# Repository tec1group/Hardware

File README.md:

This Repository is for all files that relate to the hardware of the TEC-1:
- Any expansion boards suitable for the TEC-1
- Any alternative/derivative motherboards to the TEC-1.
- and possibly any other Z80-based motherboards (eg. SC-1) and their expansions, although they should all be grouped in one folder.

<h1>How to Use this Repo</h1>
1. Make a FORK of this Repo to your own account. (You know you want to.)

That's right, make a Fork of this entire Repo back to your account.

Please keep the existing folder structure intact. If it isn't your folder, don't rename it or move it. Leave it be. Or if you don't want it, feel free to delete it from *your* Repo, but then your Pull Request (see below) may be difficult to follow/allow, if they try to remove files from the Master.

<h2>KEEPING UP TO DATE</h2>
When others add to the Repo, you'll probably want an up to date copy. (You don't have to, though.)

1. At the top right of the Repo, you will see a button called "Fetch upstream". Go on, click it...

2. You will be presented with two options, one is to "Compare" and the other is "Fetch and Merge"

3. Click on "Fetch and Merge". (If there are folders you don't care to have, you can dleete them from your own copy of the repo.)

<h2>ADDING TO THE REPO</h2>
When you want to Add or make Changes to the Repo.

1. Create a Folder in *your copy* of the Repo for each board or if it makes sense, group of boards connected to a single project.

2. Do your thing and create the hardware files in that folder; Schematics, Gerbers, documentation, PCB Layouts... Whatever it is you want to share and include into the TEC1group Hardware repository.

3. Once you are done with all your changes and ready to share it with the Group, click on the "Contribute" button and then "Open pull request".

4. A page called "Comparing changes" appears, highlighting the new files you want to add. Again, click on "Create pull request".

5. And yet another page, this time giving you the option to edit the "commit comments" that the Admins of the TEC1group will read before approval of the merge. Last time, click on "Create pull request".

6. You will be taken to the list of Pull Requests for the Repo and see how many are outstanding etc.

7. The admins of the TEC1group will review your changes and as long as you keep the changes to a folder *you* created and maintain, then there is very little reason for them to not accept the changes and pull your work back to the master Repo for all and sundry to share. THANK YOU!

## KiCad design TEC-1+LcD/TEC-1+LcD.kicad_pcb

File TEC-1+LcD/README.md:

<h1>TEC-1+LcD</h1>

This schematic and assocated files, suitable for use with KiCAD, is based on a TEC-1D with the addon of the LCD section of the DAT board.

It also has in input switch bank that can be used for user input during a program, but the main thought behind it is for setting options that would be read at startup, like what Keyboard layout to use, or what ROM to copy in.

Lastly, it makes use of the little 20 pin expander that was never used on the originals, to allow for the connection of an 8x8 or an FTDI (serial to USB) module that you can BitBang serial to.  A monitor to make use of this has yet to be written.

<b>NOTE:</b> This board has never been printed and has not been tested!  Please use at your own risk.

Change Log:<bg>
- 16/6/21 - Schematic updated to fix the LCD interface to actualy work... But the PCB has not been updated.

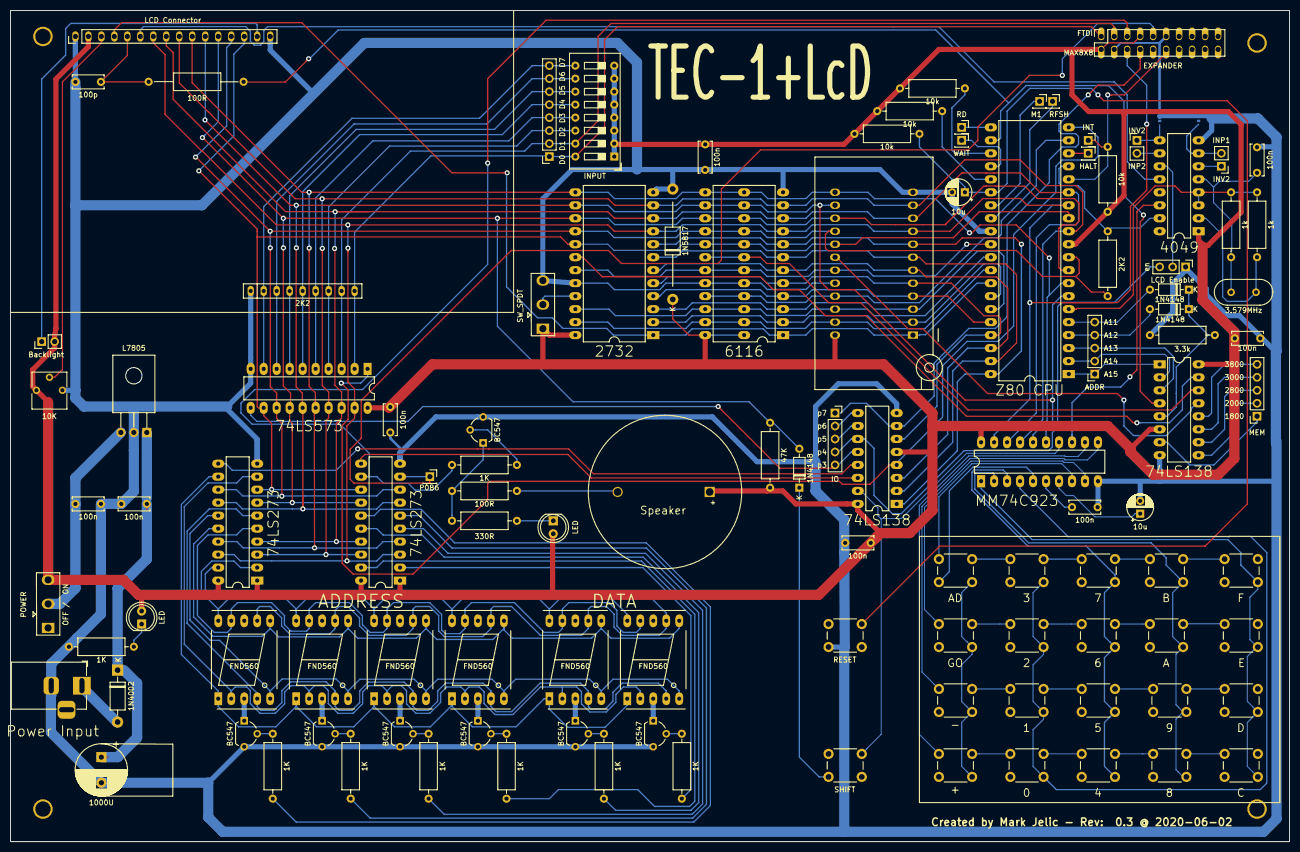
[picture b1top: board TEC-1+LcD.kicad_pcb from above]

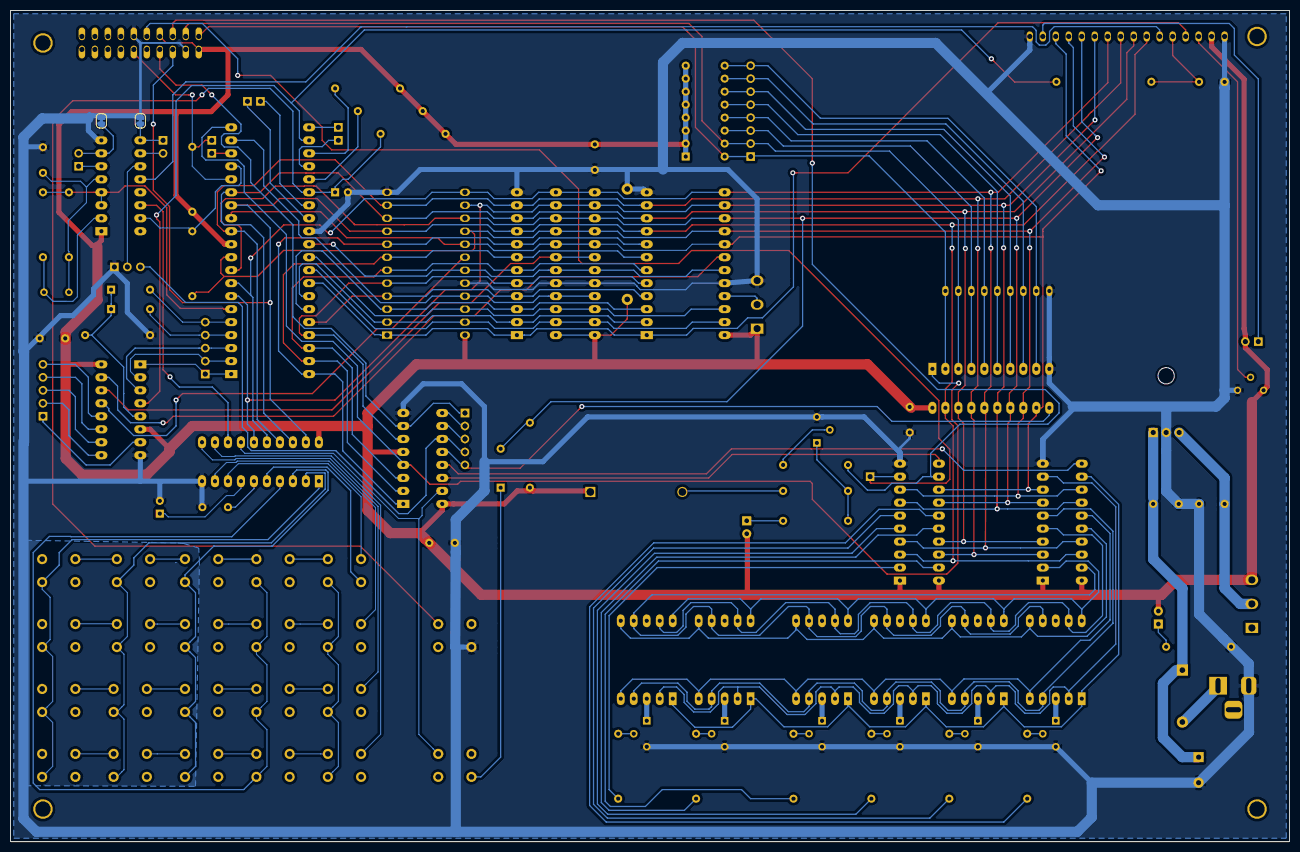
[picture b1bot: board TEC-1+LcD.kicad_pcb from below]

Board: 2 copper layers, 250.2 x 162.6 mm, 113 parts (2 on the bottom side), 143 nets.

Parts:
C1: 1000U; CP_Radial_D10.0mm_P5.00mm
C2, C3, C4, C6, C8, C10, C11, C12: 100n; C_Disc_D6.0mm_W2.5mm_P5.00mm
C5, C7: 10u; CP_Radial_D5.0mm_P2.50mm
C9: 100p; C_Disc_D6.0mm_W2.5mm_P5.00mm
D1: 1N4002; D_DO-41_SOD81_P10.16mm_Horizontal
D2: 1N5817; D_DO-41_SOD81_P22mm_Horizontal
D7, D8, D9: 1N4148; D_DO-35_SOD27_P7.62mm_Horizontal
DIG1, DIG2, DIG3, DIG4, DIG5, DIG6: FND560; 7SegmentLED_LTS6760_LTS6780
DIPSW1: INPUT; SW_DIP_SPSTx08_Slide_9.78x22.5mm_W7.62mm_P2.54mm
EX1: SOCKET; DIP_Socket-24_W11.9_W12.7_W15.24_W17.78_W18.5_3M_224-1275-0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
J1: Power Input; BarrelJack_Horizontal
J2: IO; PinSocket_1x05_P2.54mm_Vertical
J3: MEM; PinSocket_1x05_P2.54mm_Vertical
J4: INT; PinSocket_1x01_P2.54mm_Vertical
J5: M1; PinSocket_1x01_P2.54mm_Vertical
J6: RFSH; PinSocket_1x01_P2.54mm_Vertical
J7: WAIT; PinSocket_1x01_P2.54mm_Vertical
J8: HALT; PinSocket_1x01_P2.54mm_Vertical
J9: RD; PinSocket_1x01_P2.54mm_Vertical
J10: P0B6; PinSocket_1x01_P2.54mm_Vertical
J11: EXPANDER; PinSocket_2x10_P2.54mm_Vertical
J12: ADDR; PinSocket_1x05_P2.54mm_Vertical
J13: LCD Connector; PinHeader_1x16_P2.54mm_Vertical
J15, J16: INV2; PinHeader_1x02_P2.54mm_Vertical
JI1: D0 D1 D2 D3 D4 D5 D6 D7; PinSocket_1x08_P2.54mm_Vertical
JP1: LCD Enable; PinHeader_1x03_P2.54mm_Vertical
JP2: Backlight; PinHeader_1x02_P2.54mm_Vertical
JP3: INP1; SolderJumper-2_P1.3mm_Bridged_RoundedPad1.0x1.5mm
JP4: INP2; SolderJumper-2_P1.3mm_Bridged_RoundedPad1.0x1.5mm
KEY1: +; SW_Keyboard
KEY2: -; SW_Keyboard
KEY3: GO; SW_Keyboard
KEY4: AD; SW_Keyboard
KEY5: 0; SW_Keyboard
KEY6: 1; SW_Keyboard
KEY7: 2; SW_Keyboard
KEY8: 3; SW_Keyboard
KEY9: 4; SW_Keyboard
KEY10: 5; SW_Keyboard
KEY11: 6; SW_Keyboard
KEY12: 7; SW_Keyboard
KEY13: 8; SW_Keyboard
KEY14: 9; SW_Keyboard
KEY15: A; SW_Keyboard
KEY16: B; SW_Keyboard
KEY17: C; SW_Keyboard
KEY18: D; SW_Keyboard
KEY19: E; SW_Keyboard
KEY20: F; SW_Keyboard
KEY21: RESET; SW_Keyboard
KEY22: SHIFT; SW_Keyboard
LED1, LED2: LED; LED_D5.0mm
POT2: 10K; Potentiometer_Vishay_T73YP_Vertical
Q0, Q1, Q2, Q3, Q4, Q5, Q7: BC547; TO-92L_Wide
R1, R8, R9, R10, R11, R12, R13, R14: 1K; R_Axial_DIN0309_L9.0mm_D3.2mm_P12.70mm_Horizontal
R4, R5, R6, R7: 10k; R_Axial_DIN0309_L9.0mm_D3.2mm_P12.70mm_Horizontal
R15: 100R; R_Axial_DIN0309_L9.0mm_D3.2mm_P12.70mm_Horizontal
R16: 330R; R_Axial_DIN0309_L9.0mm_D3.2mm_P12.70mm_Horizontal
R17: 3.3k; R_Axial_DIN0309_L9.0mm_D3.2mm_P12.70mm_Horizontal
R18: 47K; R_Axial_DIN0309_L9.0mm_D3.2mm_P12.70mm_Horizontal
R19: 2K2; R_Axial_DIN0309_L9.0mm_D3.2mm_P12.70mm_Horizontal
R20: 100R; R_Axial_DIN0309_L9.0mm_D3.2mm_P18mm_Horizontal
R21, R22: 1k; R_Axial_DIN0309_L9.0mm_D3.2mm_P12.70mm_Horizontal
REG1: L7805; TO-126-3_Horizontal_TabUp
RN1: 2K2; R_Array_SIP9
SP1: Speaker; MagneticBuzzer_ProSignal_ABI-010-RC
SW1: POWER; SW_Slide_1P2T_CK_OS102011MS2Q
SW2: SW_SPDT; SW_Slide
U1: Z80 CPU; DIP-40_W15.24mm_LongPads
U2: 4049; DIP-16_W7.62mm_LongPads
U3, U4: 74LS138; DIP-16_W7.62mm_LongPads
U5: 2732; DIP-24_W15.24mm_LongPads
U6: 6116; DIP-24_W15.24mm_LongPads
U7: MM74C923; DIP-20_W7.62mm_LongPads
U8, U9: 74LS273; DIP-20_W7.62mm_LongPads
U11: 74LS573; DIP-20_W7.62mm_LongPads
Y1: 3.579MHz; Crystal_HC49-4H_Vertical

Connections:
+5V: C4.1, C8.1, C11.2, C12.2, D2.1, DIPSW1.1, DIPSW1.2, DIPSW1.3, DIPSW1.4, DIPSW1.5, DIPSW1.6, DIPSW1.7, DIPSW1.8, EX1.24, J11.2, J11.7, J13.2, JP2.2, LED1.2, LED2.2, POT2.3, R4.2, R5.1, R6.1, R7.2, R18.1, SP1.1, SW1.3, SW2.1, U1.11, U2.1, U3.6, U3.16, U4.5, U4.16, U5.24, U6.24, U7.20, U8.1, U8.20, U9.1, U9.20, U11.20
/A: DIG1.7, DIG2.7, DIG3.7, DIG4.7, DIG5.7, DIG6.7, U8.19
/A0: EX1.8, U1.40, U4.1, U5.8, U6.8
/A1: EX1.7, U1.39, U4.2, U5.7, U6.7
/A2: EX1.6, U1.38, U4.3, U5.6, U6.6
/A3: EX1.5, U1.37, U4.6, U5.5, U6.5
/A4: EX1.4, U1.36, U5.4, U6.4
/A5: EX1.3, U1.35, U5.3, U6.3
/A6: EX1.2, U1.34, U5.2, U6.2
/A7: EX1.1, J13.4, U1.33, U5.1, U6.1
/A8: EX1.23, U1.32, U5.23, U6.23
/A9: EX1.22, U1.31, U5.22, U6.22
/A10: EX1.19, U1.30, U5.19, U6.19
/B: DIG1.6, DIG2.6, DIG3.6, DIG4.6, DIG5.6, DIG6.6, U8.16
/C: DIG1.4, DIG2.4, DIG3.4, DIG4.4, DIG5.4, DIG6.4, U8.6
/CTS: J10.1, J11.9, U9.9
/D: DIG1.2, DIG2.2, DIG3.2, DIG4.2, DIG5.2, DIG6.2, U8.9
/D0: EX1.9, J11.6, J13.7, U1.14, U5.9, U6.9, U7.19, U8.18, U9.3, U11.19
/D1: EX1.10, J13.8, U1.15, U5.10, U6.10, U7.18, U8.4, U9.17, U11.18
/D2: EX1.11, J13.9, U1.12, U5.11, U6.11, U7.17, U8.3, U9.18, U11.17
/D3: EX1.13, J13.10, U1.8, U5.13, U6.13, U7.16, U8.17, U9.4, U11.16
/D4: EX1.14, J13.11, U1.7, U5.14, U6.14, U7.15, U8.14, U9.7, U11.15
/D5: D7.2, EX1.15, J13.12, R18.2, U1.9, U5.15, U6.15, U8.7, U9.14, U11.14
/D6: EX1.16, J13.13, R19.2, U1.10, U5.16, U6.16, U8.13, U9.8, U11.13
/D7: EX1.17, J13.14, U1.13, U5.17, U6.17, U8.8, U9.13, U11.12
/DP: DIG1.5, DIG2.5, DIG3.5, DIG4.5, DIG5.5, DIG6.5, U8.15
/E: DIG1.1, DIG2.1, DIG3.1, DIG4.1, DIG5.1, DIG6.1, U8.12
/F: DIG1.9, DIG2.9, DIG3.9, DIG4.9, DIG5.9, DIG6.9, U8.5
/G: DIG1.10, DIG2.10, DIG3.10, DIG4.10, DIG5.10, DIG6.10, U8.2
/RX: DIPSW1.15, J11.3, JI1.2, RN1.8, U11.3
/TX: J11.5, R14.2, U9.12
GND: C1.2, C2.2, C3.2, C4.2, C5.2, C6.2, C7.2, C8.2, C9.1, C10.2, C11.1, C12.1, D2.2, EX1.12, EX1.20, J1.2, J11.4, J11.11, J13.1, J13.16, JP1.1, JP3.1, JP4.1, KEY21.3, POT2.1, Q0.3, Q1.3, Q2.3, Q3.3, Q4.3, Q5.3, Q7.3, R1.2, R17.1, REG1.2, RN1.1, SW2.3, U1.29, U2.8, U3.8, U4.8, U5.12, U5.20, U6.12, U6.20, U7.10, U8.10, U9.10, U11.10
unnamed: C1.1, C2.1, D1.1, REG1.1
unnamed: C3.1, REG1.3, SW1.2
unnamed: C5.1, KEY21.2, R7.1, U1.26
unnamed: C6.1, U7.6
unnamed: C7.1, U7.7
unnamed: C9.2, J13.5, R20.2
unnamed: C10.1, R22.1, U2.5, Y1.1
unnamed: D1.2, J1.1
unnamed: D7.1, KEY22.3
unnamed: D8.1, D9.1, R17.2, U3.5
unnamed: D8.2, J12.4, U1.4
unnamed: D9.2, J12.5, U1.5
unnamed: DIG1.3, Q5.1
unnamed: DIG2.3, Q4.1
unnamed: DIG3.3, Q3.1
unnamed: DIG4.3, Q2.1
unnamed: DIG5.3, Q1.1
unnamed: DIG6.3, Q0.1
unnamed: DIPSW1.9, JI1.8, RN1.2, U11.9
unnamed: DIPSW1.10, JI1.7, RN1.3, U11.8
unnamed: DIPSW1.11, JI1.6, RN1.4, U11.7
unnamed: DIPSW1.12, JI1.5, RN1.5, U11.6
unnamed: DIPSW1.13, JI1.4, RN1.6, U11.5
unnamed: DIPSW1.14, JI1.3, RN1.7, U11.4
unnamed: DIPSW1.16, J11.1, JI1.1, RN1.9, U11.2
unnamed: EX1.18, U3.13
unnamed: EX1.21, U1.19, U6.21
unnamed: J2.2, U4.9
unnamed: J2.3, U4.10
unnamed: J2.4, JP1.3, U4.11
unnamed: J2.5, U4.12, U11.11
unnamed: J3.1, U3.7
unnamed: J3.2, U3.9
unnamed: J3.3, U3.10
unnamed: J3.4, U3.11
unnamed: J3.5, U3.12
unnamed: J5.1, U1.27
unnamed: J6.1, U1.28
unnamed: J7.1, U1.24
unnamed: J8.1, U1.18
unnamed: J9.1, U1.21
unnamed: J2.1, J11.8, U4.7
unnamed: J4.1, J11.12, R6.2, U1.16
unnamed: J12.1, U1.1, U3.1
unnamed: J12.2, U1.2, U3.2
unnamed: J12.3, U1.3, U3.3
unnamed: J13.3, POT2.2
unnamed: J13.6, U2.12
unnamed: J13.15, JP2.1
unnamed: J15.1, U2.6
unnamed: J15.2, JP3.2, U2.7
unnamed: J16.1, JP4.2, U2.9
unnamed: J16.2, U2.10
unnamed: JP1.2, U2.11
unnamed: KEY1.1, U7.12
unnamed: KEY1.2, KEY5.1
unnamed: KEY1.4, KEY2.4, KEY3.4, KEY4.4
unnamed: KEY2.1, U7.11
unnamed: KEY2.2, KEY6.1
unnamed: KEY3.1, U7.9
unnamed: KEY3.2, KEY7.1
unnamed: KEY4.1, U7.8
unnamed: KEY4.2, KEY8.1
unnamed: KEY4.3, U7.5
unnamed: KEY5.2, KEY9.1
unnamed: KEY5.4, KEY6.4, KEY7.4, KEY8.4, U7.4
unnamed: KEY6.2, KEY10.1
unnamed: KEY10.2, KEY14.1
unnamed: KEY9.4, KEY10.4, KEY11.4, KEY12.4, U7.3
unnamed: KEY7.2, KEY11.1
unnamed: KEY11.2, KEY15.1
unnamed: KEY8.2, KEY12.1
unnamed: KEY12.2, KEY16.1
unnamed: KEY9.2, KEY13.1
unnamed: KEY13.2, KEY17.1
unnamed: KEY13.4, KEY14.4, KEY15.4, KEY16.4, U7.2
unnamed: KEY14.2, KEY18.1
unnamed: KEY15.2, KEY19.1
unnamed: KEY16.2, KEY20.1
unnamed: KEY17.4, KEY18.4, KEY19.4, KEY20.4, U7.1
unnamed: KEY22.2, U4.15, U7.14
unnamed: LED1.1, R1.1
unnamed: LED2.1, R16.1
unnamed: Q0.2, R8.2
unnamed: Q1.2, R9.2
unnamed: Q2.2, R10.2
unnamed: Q3.2, R11.2
unnamed: Q4.2, R12.2
unnamed: Q5.2, R13.2
unnamed: Q7.1, R15.2, R16.2
unnamed: Q7.2, R14.1
unnamed: R4.1, U1.25
unnamed: R5.2, U1.23
unnamed: R8.1, U9.2
unnamed: R9.1, U9.16
unnamed: R10.1, U9.19
unnamed: R11.1, U9.5
unnamed: R12.1, U9.6
unnamed: R13.1, U9.15
unnamed: R15.1, SP1.2
unnamed: R19.1, U1.17, U2.15
unnamed: R20.1, U1.22, U3.4
unnamed: R21.1, U2.2, Y1.2
unnamed: R21.2, R22.2, U1.6, U2.3, U2.4
unnamed: SW2.2, U5.21
unnamed: U1.20, U4.4, U11.1
unnamed: U2.14, U7.13
unnamed: U3.14, U6.18
unnamed: U3.15, U5.18
unnamed: U4.13, U8.11
unnamed: U4.14, U9.11

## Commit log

2020-05-22 Update LICENSE
2020-06-06 Create folder
2020-06-06 TEC-1+LcD KiCAD Project
    A KiCad project that has both a schematic and a 2 layer PCB of the TEC-1D combined with an LCD module.
2021-06-14 How to use this Repo
    Created this file to outline how people should use this Repo.
2021-06-16 Added files related to MAX7219
    Two ASM files and picture of how I connected it to the Cathode latch
2021-06-16 All files relating to the TEC-1+LcD
    The PCB file DOES NOT match the schematic as of this upload.
    The schematic was updated today to make the LCD actually work. Now the PCB needs updating... In the coming days.
2021-10-03 Schematic PDF
2023-03-12 Excel version of hardware add-ons list
    Excel version List of hardware add-ons produced by TE & various TEC and SC users.
